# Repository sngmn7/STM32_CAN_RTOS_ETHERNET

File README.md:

# STM32 CAN · Ethernet · FreeRTOS 기반 Zonal E/E Architecture

> STM32 다중 노드와 Jetson을 연계하여 차량의 Zonal E/E Architecture를 축소 구현한 프로젝트입니다.  
> CAN 기반 노드 통신, Ethernet/UDP 기반 상위 시스템 연동, FreeRTOS 실시간 제어, Linux Character Device Driver, DTC 진단, GUI 모니터링, 4-Layer PCB 설계·제작까지 전체 시스템을 직접 구현하고 검증했습니다.

---

## 1. Project Overview

기존의 기능 중심 MCU 프로젝트에서 확장하여, 여러 제어기가 통신을 통해 협력하는 차량 분산 제어 구조를 구현하는 것을 목표로 진행했습니다.

각 Zone 내부에서는 **CAN**을 이용해 센서·제어·상태 정보를 교환하고, Zone Controller에서 수집한 정보는 **Ethernet/UDP**를 통해 상위 시스템인 Jetson으로 전달하도록 구성했습니다.

또한 시스템 규모가 커지면서 발생하는 통신 오류, 실시간성 문제, 고장 진단 문제를 직접 분석하고 검증했습니다.

### 주요 구현 내용

- STM32 기반 다중 노드 Zonal Architecture 구성
- CAN 기반 Zone 내부 통신
- Ethernet/UDP 기반 STM32 ↔ Jetson 연동
- V-Cycle 관점의 요구사항 및 검증 기준 정의
- CAN ID / Data Structure 기반 ICD 작성
- FreeRTOS 기반 실시간 Task 구조 구현
- Linux Character Device Driver 구현
- DTC 기반 고장 진단 시스템
- GUI 기반 시스템 상태 모니터링
- CAN/Ethernet End-to-End Latency 계측
- KiCad 기반 4-Layer PCB 설계 및 실제 제작
- 반복시험 및 자동화된 검증 환경 구성

---

## 2. System Architecture

```text
                  ┌────────────────────────────┐
                  │       Jetson / Linux       │
                  │                            │
                  │  Character Device Driver   │
                  │  DTC / GUI / Monitoring    │
                  └─────────────┬──────────────┘
                                │
                         Ethernet / UDP
                                │
            ┌───────────────────┴───────────────────┐
            │                                       │
┌───────────▼───────────┐               ┌───────────▼───────────┐
│ Front Zone Controller │               │ Rear Zone Controller  │
│     STM32H723         │               │      STM32H723        │
└───────────┬───────────┘               └───────┬─────────┬─────┘
            │ CAN                               │ CAN     │ CAN
            │                                   │         │
     ┌──────▼──────┐                     ┌──────▼───┐ ┌──▼──────────┐
     │ Front Node  │                     │Rear Node │ │Rear Body    │
     │ STM32F407   │                     │STM32F446 │ │STM32F407   │
     └─────────────┘                     └──────────┘ └─────────────┘
```

### 통신 구조
- Zone 내부의 MCU 간 상태 및 제어 데이터 교환
- 센서 데이터 전달
- DTC 및 성능 계측 데이터 전달
- GUI/HMI와 임베디드 제어 시스템 연동

---

## 3. Repository Structure

```text
STM32_CAN_RTOS_ETHERNET/
│
├── Node_F407_Front/
│   └── Front Zone I/O Node
│
├── Node_F407_Rear/
│   └── Rear Body Node
│
├── Node_F447_Rear/
│   └── Rear Zone Sensor Node
│       ※ 실제 MCU는 STM32F446 계열
│
├── ZoneController_Front_H723/
│   └── Front Zone Controller
│
├── ZoneController_Rear_H723_real/
│   └── Rear Zone Controller
│
├── jetson_device_driver/
│   └── Linux Character Device Driver
│
├── jetson_device_driver_lcd/
│   └── I2C LCD Character Device Driver
│
├── rear_node_board/
│   └── KiCad 4-Layer PCB 설계 및 제조 데이터
│
├── DEBUG_JOURNAL_최종/
│   └── Debug / Measurement / Verification Records
│
└── README.md
```

---

# 4. CAN Communication

- 노드별 송수신 역할 정의
- Bit Timing 설정
- CAN Filter 구성
- CAN 상태 및 오류 계측
- 정상/이상 네트워크 비교 검증

---

## 4.1 CAN Frame Loss 47% → 0%

시스템 검증 과정에서 특정 500 kbps CAN Bus에서 수신 프레임의 약 47%가 유실되는 문제가 발생했습니다.

단순히 코드를 수정하기보다 정상 동작하는 CAN 네트워크와 문제가 발생하는 네트워크의 설정을 비교했습니다.

그 결과 두 노드의 **Bit Timing과 Sample Point가 서로 다르게 설정되어 있음**을 확인했습니다.

설정을 정합한 뒤 다시 시험한 결과 프레임 유실률을 0%까지 개선했습니다.

```text
Before : Frame Loss 47 %
After  : Frame Loss 0 %
```

이 경험을 통해 통신 오류 발생 시 정상 시스템을 대조군으로 두고 설정과 데이터를 단계적으로 비교하는 방식의 중요성을 확인했습니다.

---

# 5. Ethernet / UDP Communication

각 Zone에서 수집한 데이터를 상위 시스템인 Jetson으로 전달하기 위해 Ethernet을 사용했습니다.

### 수행 내용

- STM32H723 Ethernet 설정
- lwIP 기반 UDP 통신
- Zone Controller → Jetson Telemetry 전달
- Jetson → Zone Controller Command 전달
- Zone 간 정보 전달
- DTC 및 성능 계측 데이터 전송

CAN은 **Zone 내부의 실시간 데이터 교환**, Ethernet은 **상위 시스템과의 데이터 연동**에 사용하도록 역할을 분리했습니다.

---

# 6. End-to-End Latency Optimization

센서 입력부터 Jetson 상위 시스템까지 데이터가 전달되는 전체 경로를 측정한 결과 최대 **150.6 ms**의 지연이 발생했습니다.

처음에는 개별 코드의 연산시간을 의심했지만, 구간별 시간을 직접 측정한 결과 기존의 **주기 처리 방식**에서 데이터가 준비된 뒤에도 다음 처리 시점까지 대기하는 시간이 반복되고 있음을 확인했습니다.

이에 상행/하행 데이터 처리를 필요한 이벤트가 발생했을 때 수행하도록 **Event Trigger 방식**으로 변경했습니다.

| 항목 | 개선 전 | 개선 후 |
|---|---:|---:|
| 최대 End-to-End Latency | 150.6 ms | 27.5 ms |
| 평균 End-to-End Latency | 65.5 ms | 6.0 ms |
| 최대 지연 개선 | - | **81.7% 감소** |

단순히 코드를 빠르게 만드는 것이 아니라 전체 데이터 흐름을 측정하고 병목 구조를 변경하는 방식으로 문제를 해결했습니다.

---

# 7. FreeRTOS

STM32 Zone Controller의 기능을 Task 단위로 분리하고 실시간 시스템의 동작을 검증하기 위해 FreeRTOS를 적용했습니다.

### 주요 내용

- Task Priority 설계
- Semaphore
- Mutex
- Task Notification
- 공유 자원 동기화
- Stack Usage 계측
- Priority Inversion 검증
- Priority Inheritance 적용

---

## 7.1 Priority Inversion

공유 자원에 접근하는 여러 Task가 동시에 동작할 때 높은 우선순위 Task가 즉시 수행되지 못하는 Priority Inversion 상황을 구성하고 직접 계측했습니다.

Binary Semaphore와 Mutex 사용 시의 차이를 비교했습니다.

| 방식 | 최대 지연 |
|---|---:|
| Semaphore / Priority Inheritance 없음 | 7,096 μs |
| Mutex / Priority Inheritance 적용 | 2,068 μs |

Priority Inheritance를 적용해 지연시간을 약 **3.4배 감소**시켰습니다.

이를 통해 RTOS에서 Task Priority만 설정하는 것뿐 아니라 공유 자원의 동기화 방식까지 실시간 성능에 영향을 준다는 점을 확인했습니다.

---

# 8. FreeRTOS Debugging

FreeRTOS 전환 과정에서는 단순 HardFault가 아닌 Kernel 정지 현상도 경험했습니다.

초기에는 assert가 발생한 위치를 각각 수정했지만 문제 발생 위치가 계속 바뀌었습니다.

이를 메모리 오염 가능성으로 판단하고 Stack Overflow Hook과 High Water Mark를 추가해 Task별 Stack 사용량을 측정했습니다.

그 결과 Ethernet Interface Thread의 Stack이 실제 필요량보다 작게 설정되어 있었음을 확인했습니다.

### 원인

CMSIS-RTOS v2의 `stack_size` 단위를 잘못 해석해 Stack 공간이 부족하게 설정되어 있었습니다.

Stack 크기를 조정한 뒤 반복 시험을 통해 Kernel 정지와 Stack Overflow가 발생하지 않음을 확인했습니다.

이 과정은 `DEBUG_JOURNAL_최종/`에 기록되어 있습니다.

---

# 9. DTC Diagnostic System

시스템 이상이 발생할 때마다 여러 MCU와 통신 로그를 각각 확인해야 해 원인을 파악하는 데 시간이 걸렸습니다.

이를 개선하기 위해 각 노드의 고장 상태를 **DTC(Diagnostic Trouble Code)** 형태로 코드화했습니다.

### 구현 내용

- Node Fault 상태 정의
- DTC Code 정의
- Pending / Confirmed 상태 관리
- CAN Fault Monitoring
- 통신 Timeout Detection
- Ethernet을 통한 DTC 전달
- Jetson GUI에서 Fault 상태 표시
- 반복시험을 통한 진단 결과 검증

---

## 9.1 CAN Link Failure Detection

초기에는 CAN Bus-Off 상태만으로 통신 이상을 판정했습니다.

하지만 실제 CAN Link가 끊겨도 Bus-Off에 진입하지 않아 고장을 감지하지 못하는 경우가 발생했습니다.

이에 Bus-Off뿐 아니라 **수신 데이터 Timeout**을 함께 진단 조건으로 사용하도록 수정했습니다.

```text
CAN Link Failure Detection

Before : 일부 링크 단절 검출 불가
After  : 약 500 ms 이내 검출
```

단순 오류 Flag에만 의존하지 않고 실제 통신 상태까지 함께 확인하도록 진단 기준을 변경했습니다.

---

# 10. GUI / HMI Monitoring

Jetson에서 각 Zone의 상태를 통합해 확인할 수 있도록 GUI 기반 HMI를 구현했습니다.

### 확인 정보

- Zone 상태
- CAN 상태
- 센서 데이터
- DTC
- 통신 상태
- Fault 위치
- System Telemetry

이를 통해 고장 발생 시 여러 Node의 로그를 각각 확인하기 전에 GUI에서 먼저 이상 위치와 상태를 파악할 수 있도록 구성했습니다.

반복적인 Closed-Loop 시험을 통해 HMI와 실제 시스템 동작을 검증했습니다.

---

# 11. Linux Character Device Driver

Jetson Linux 환경에서 Kernel Space와 User Space 간 HW/SW Interface를 직접 구현하기 위해 Character Device Driver를 작성했습니다.

---

## 11.1 I2C LCD Driver

PCF8574 기반 I2C LCD를 제어하는 Linux Character Device Driver를 구현했습니다.

### 구현 내용

- `i2c_driver`
- `probe()` / `remove()`
- Character Device 등록
- `/dev` Interface 제공
- `open`
- `write`
- `ioctl`
- Mutex 기반 동기화
- LCD Command 처리

User Space Application이 `/dev`를 통해 LCD 기능을 사용할 수 있도록 구성했습니다.

---

## 11.2 UDP Status Driver

Zone Controller에서 전달되는 UDP Telemetry를 Linux Kernel에서 수신하고 `/dev` Interface를 통해 User Space에 제공하는 Driver를 구현했습니다.

### 구현 내용

- Kernel UDP Socket
- Kernel Thread
- Blocking Read
- Wait Queue
- Spinlock
- `poll()`
- Packet Validation
- Sequence Monitoring

초기에는 SocketCAN Network Device 형태로 구현하려 했지만, CAN Subsystem이 요구하는 초기화 조건을 충족하지 못해 Kernel이 정지하는 문제가 발생했습니다.

Kernel UDP Socket과 Thread는 정상 동작하고 있음을 확인한 뒤 Network Device 등록 계층을 분리해 문제를 좁혔고, Character Device 방식으로 변경해 해결했습니다.

---

# 12. PCB Design & Manufacturing

초기 시스템은 Breadboard와 Jumper Wire를 이용해 구성했습니다.

프로젝트가 커지면서 다음 문제가 반복적으로 발생했습니다.

- 접촉 불량
- 배선 복잡도 증가
- CAN 배선 오류 가능성
- 재현성이 낮은 HW 구성

이를 개선하기 위해 KiCad를 이용해 **4-Layer Custom PCB를 직접 설계하고 실제 제작업체에 제조를 의뢰했습니다.**

### 수행 과정

1. 기존 배선 및 Pin Map 정리
2. 회로도 작성
3. CAN Transceiver 회로 구성
4. CAN Termination 설계
5. Sensor / Actuator Interface 설계
6. Power / Signal Net 정의
7. Footprint 배치
8. 4-Layer Stack 구성
9. Routing
10. ERC / DRC 검증
11. Gerber 및 Drill File 생성
12. 외부 PCB 제조 의뢰
13. 실제 보드 제작 및 시스템 적용

---

## 12.1 CAN Hardware Design

CAN 통신부에는 SN65HVD230 기반 CAN Transceiver와 Split Termination 구조를 적용했습니다.

Rear CAN Network에서는 3개의 Node가 연결되므로 버스의 양 끝 Node에만 Termination을 적용할 수 있도록 Jumper 구조를 구성했습니다.

센서, LED, Switch 및 기타 I/O 회로도 PCB에 통합했습니다.

PCB 관련 설계 파일 및 제조 데이터는 아래 폴더에 있습니다.

```text
rear_node_board/
```

---

# 13. V-Cycle & ICD

프로젝트 규모가 커지면서 여러 Node의 기능과 통신 기준을 기억에 의존해 관리하기 어려워졌습니다.

이에 V-Cycle 관점에서 요구사항과 검증 기준을 정리했습니다.

### 수행 내용

- System Requirement 정의
- Functional Requirement 분해
- 검증 기준 작성
- CAN ID 정의
- CAN Data Structure 정의
- UDP Packet 정의
- Interface Control Document 작성
- Test Case 구성
- 요구사항 ↔ 검증 항목 연결

기능 구현 이후 시험 방법을 생각하는 것이 아니라 요구사항 정의 단계에서 검증 방법까지 함께 고려하도록 개발 방식을 정리했습니다.

---

# 14. Debugging & Verification

프로젝트 과정에서 발생한 문제와 분석 과정을 별도의 Debug Journal로 관리했습니다.

```text
DEBUG_JOURNAL_최종/
```

### 주요 Debugging 사례

- CAN Frame Loss
- CAN Bit Timing / Sample Point 문제
- Ethernet Power-On Failure
- FreeRTOS Stack Overflow
- Priority Inversion
- DTC False Detection
- CAN Link Failure Detection
- UDP Telemetry 검증
- Network IP / Subnet 문제
- Sensor Data 이상
- Closed-Loop System Verification

단순히 해결 결과만 기록하지 않고 아래와 같은 형태로 관리했습니다.

```text
Problem
  ↓
Hypothesis
  ↓
Measurement
  ↓
Root Cause
  ↓
Modification
  ↓
Regression Test
```

---

# 15. Measurement & Verification

시스템 동작을 감으로 판단하지 않고 가능한 항목은 실제 데이터를 측정해 검증했습니다.

### 대표 검증 항목

| 항목 | 결과 |
|---|---:|
| CAN Frame Loss | 47% → 0% |
| End-to-End Maximum Latency | 150.6 ms → 27.5 ms |
| End-to-End Average Latency | 65.5 ms → 6.0 ms |
| Priority Inversion Delay | 7,096 μs → 2,068 μs |
| CAN Link Failure Detection | 검출 불가 → 약 500 ms |
| DTC 반복 검출 편차 | 약 1.5 ms 수준 |
| HMI Closed-Loop Test | 8 / 8 Pass |

---

# 16. Tech Stack

### Embedded

- STM32H723
- STM32F407
- STM32F446
- C
- STM32CubeIDE
- STM32 HAL
- FreeRTOS
- CMSIS-RTOS2

### Communication

- CAN
- FDCAN
- Ethernet
- UDP
- I2C
- RS485

### Linux

- Jetson
- Linux Kernel Module
- Character Device Driver
- Kernel UDP Socket
- Kernel Thread
- `/dev` Interface

### Hardware

- KiCad
- 4-Layer PCB
- CAN Transceiver
- Gerber
- BOM
- PCB Manufacturing

### System Engineering

- V-Cycle
- ICD
- DTC
- Test Case
- System Integration
- Verification
- Debugging

---

# 17. Key Takeaways

이 프로젝트에서는 단순히 MCU의 기능을 구현하는 것을 넘어 여러 장치가 연결된 시스템 전체를 설계하고 검증했습니다.

특히 다음을 직접 경험했습니다.

- CAN / Ethernet 기반 분산 통신 구조 설계
- 통신 오류의 Root Cause 분석
- FreeRTOS 기반 실시간 시스템 설계
- Task Synchronization 및 Priority Inversion 검증
- Linux Kernel Device Driver 구현
- DTC 기반 고장 진단
- GUI 기반 상태 모니터링
- V-Cycle과 ICD를 활용한 Interface 관리
- 4-Layer PCB 설계 및 실제 제작
- HW / FW / Linux를 포함한 전체 시스템 통합
- 측정 데이터를 기반으로 한 성능 개선 및 Regression Test

기능이 한 번 동작하는 것보다 **문제가 발생했을 때 원인을 추적할 수 있고, 수정한 결과를 다시 검증할 수 있는 시스템을 만드는 것**을 목표로 프로젝트를 진행했습니다.

---

## Author

**Lee Seungmin**

- Kyungpook National University
- Department of Electronics Engineering
- CAN ID 대역 정의
- 메시지별 Data Structure 정의
각 Zone 내부의 MCU 간 통신은 CAN을 기반으로 구성했습니다.

### 수행 내용
- 액추에이터 명령 전달
- 고장 및 상태 정보 전달

**Ethernet / UDP**
- 각 Zone Controller에서 수집한 데이터를 Jetson으로 전달
- 상위 시스템 명령 전달

CAN과 Ethernet은 서로 다른 역할로 사용했습니다.
**CAN**

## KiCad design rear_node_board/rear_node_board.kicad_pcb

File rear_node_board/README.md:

# REAR NODE BOARD — STM32F446RET6 ×2

Rear 존의 말단 두 노드를 **한 장의 PCB**로 합친 보드.
H723 존 컨트롤러는 **Nucleo-144 모듈 그대로** 두고 J2 로 연결한다.

```
[H723 Nucleo-144]  ── J2 (CAN 로직신호 4 + GND) ──┐
                                                   │
   ┌───────────────── REAR NODE BOARD ─────────────┴──────────────┐
   │  U3 ─ CAN500 ─ U4 ─ U1 (F446RET6, rear body)                 │
   │  U5 ─ CAN250 ─ U6 ─ U2 (F446RET6, 센서/램프 노드)             │
   │                        └ LED×4, 스위치, HC-SR04, BNO085      │
   └──────────────────────────────────────────────────────────────┘
              │
        J5 ── REAR-CAN-H 500k → 모터 노드(외부)
```

**검증 상태**: ERC **0 errors / 0 warnings**, 배치검사 통과,
두 MCU **각각 64/64 핀 전부 연결**(미연결은 트랜시버 Vref ×4, 의도된 NC).

### 배선 방식

**436개 배선 + 51개 정션**으로 실제 선이 그려져 있다. 라벨만 띄워놓은 게 아니다.

| 실선으로 그린 것 | 방식 |
|---|---|
| CAN 500k / 250k 버스 | 세로 트렁크 + 각 노드로 가지 + 정션 |
| 종단 5세트 | JP→60R→중점→60R→CANL 직렬 체인, 중점에서 4.7nF→GND |
| LED 4개 | 저항→애노드 실선, 캐소드→GND |
| 크리스탈 2개 | 크리스탈↔로드캡 실선, 캡→GND |
| 스위치 + 풀업 | 같은 노드로 실선 결선 |
| 디커플링 15개 | 위쪽 +3V3 레일 / 아래쪽 GND 레일 실선 + 정션 |

**MCU 두 개만 네트 라벨을 쓴다.** 핀 128개를 시트 전체로 배선하면 오히려
읽을 수 없어지기 때문이고, 이건 실무 회로도의 표준 방식이다.
전기적 연결은 동일하며 네트리스트로 검증했다.

### ★ 네트 라벨 = 실제 배선이다

**PCB 는 회로도의 선 그림을 보지 않는다. 네트리스트만 읽는다.**
그래서 라벨로 연결하든 선으로 연결하든 PCB 결과는 완전히 같다.

이것을 말이 아니라 실물로 확인했다 — 이 회로도에서 PCB 를 실제로 생성했다.

```
netlist : 83 components, 136 nets
placed  : 83 footprints        <- 누락 0
nets    : 136 on board, 404 pads assigned
DRC     : 0 violations, 266 unconnected items
```

`266 unconnected items` 가 바로 **rats nest** 다. pcbnew 가 "이 266 개를
연결해야 한다"고 인식했다는 뜻이고, 곧 MCU 핀을 포함한 모든 연결이
정상적으로 넘어갔다는 증거다.

예를 들어 U2(F446) 의 핀들은 PCB 에서 이렇게 이어진다.

```
pin 11  TOGGLE_SW  -> R18.2, SW1.1
pin 14  LED_LEFT   -> R14.1
pin 30  ND_VCAP1   -> C27.1
pin 44  ND_CAN_RX  -> U6.4
pin 61  I2C1_SCL   -> J8.3, R19.2
pin  2  ND_PC13    -> J14.1
```

**64 핀 전부가 이런 식으로 연결돼 있다.**

---

## 1. 왜 F446 두 개인가

원래 rear body 노드는 F407VG(LQFP100)였지만 F446RET6(LQFP64)로 통일했다.

| | 통일 전 | 통일 후 |
|---|---|---|
| MCU 종류 | F407VG + F446RE | **F446RE ×2** |
| 풋프린트 | LQFP100 + LQFP64 | **LQFP64 ×2** |
| 지원회로 | VCAP 2개 + 1개, 서로 다름 | **완전 동일** |
| BOM 라인 | 2 | **1** |

> ⚠️ **펌웨어 이식 필요**: F407 rear body 펌웨어는 CAN1 이 **PD0/PD1** 이었다.
> F446 LQFP64 에는 그 핀이 없어 **PA11/PA12** 로 옮겨야 한다.
> 현재 rear body 는 500k ping/echo(0x101→0x181)만 하므로 이식 부담은 작다.

---

## 2. 보드 구성

| 참조 | 부품 | 역할 |
|---|---|---|
| U1 | STM32F446RET6 | rear body 노드, 500k 버스 |
| U2 | STM32F446RET6 | 센서/램프 노드, 250k 버스 |
| U3 | SN65HVD230 | H723 FDCAN1 ↔ 500k |
| U4 | SN65HVD230 | U1 ↔ 500k |
| U5 | SN65HVD230 | H723 FDCAN2 ↔ 250k |
| U6 | SN65HVD230 | U2 ↔ 250k |
| U7 | AMS1117-3.3 | 5V → 3.3V |
| Y1, Y2 | 8 MHz | HSE |
| JP1~JP5 | 종단 점퍼 | 아래 §3 |

### 커넥터

| 참조 | 용도 | 핀 |
|---|---|---|
| J1 | VIN 5 V | 스크류터미널 2 |
| J2 | **H723 Nucleo** (FDCAN1 TX/RX, FDCAN2 TX/RX, GND×2) | 6 |
| J3 / J4 | SWD (U1 / U2) — 3V3, SWCLK, GND, SWDIO, **NRST**, SWO | 6 |
| J5 | REAR-CAN-H 500k → 모터 노드 | 3 |
| J6 | REAR-CAN-L 250k 예비 | 3 |
| J7 | HC-SR04 (**5 V**) | 4 |
| J8 | BNO085 IMU | 6 |
| J9 | UART 콘솔 (U2) | 3 |
| J10~J13 | U1 브레이크아웃 (43핀 전부) | 12/12/12/11 |
| J14~J16 | U2 브레이크아웃 (30핀 전부) | 12/12/9 |

---

## 3. ★ 종단 점퍼 — 이것만은 틀리면 안 됨

| 버스 | 드롭 | 점퍼 | 기본 |
|---|---|---|---|
| REAR-CAN-H 500k | **3개** (H723, U1, 모터노드) | JP1 (H723) | **삽입** |
| | | JP2 (U1, 버스 중간) | **개방** |
| | | JP3 (모터노드 쪽) | **삽입** |
| REAR-CAN-L 250k | 2개 | JP4, JP5 | **둘 다 삽입** |

3개를 다 끼우면 40 Ω 이 되어 드라이버가 규정 차동전압을 못 만들고 통신이 깨진다.
종단은 스플릿(60 Ω + 60 Ω, 중점 4.7 nF → GND) 방식.

---

## 4. 조립 시 반드시 지킬 것

**① C26 / C27 (VCAP, 각 MCU 30번핀) — 필수**
내부 레귤레이터 안정화용. 없거나 멀면 **칩이 아예 부팅하지 않는다.**
디커플링처럼 "있으면 좋은" 부품이 아니다. 핀 바로 옆에 배치할 것.

**② R2 / R3 (BOOT0 풀다운, 각 60번핀) — 필수**
빠지면 플래시 부팅이 안 되고 무작위로 시스템 부트로더로 들어간다.
커스텀 보드 첫 제작에서 가장 흔한 실패 원인.

**③ SWD 헤더에 NRST 포함**
클럭 설정을 잘못 넣었을 때 connect-under-reset 으로만 살릴 수 있다.
NRST 가 없으면 그대로 벽돌이 된다.

**④ VDD 핀마다 100 nF**
MCU 하나당 VDD 4개(19, 32, 48, 64) → 각각 바로 옆에.

**⑤ J2 의 GND 를 반드시 연결**
H723 Nucleo 는 자기 전원을 쓰지만, 트랜시버가 기준 전위를 공유해야
CAN 이 성립한다. GND 미공통이 CAN 무응답의 가장 흔한 원인이다.

---

## 5. 펌웨어 쪽 확인 사항

**클럭을 HSE 로 바꿔야 한다.**
현재 F446 펌웨어 `SystemClock_Config()` 는 HSI 를 쓴다
(`RCC_OSCILLATORTYPE_HSI`, PLLM=16, PLLN=336, PLLP=4 → 84 MHz).

STM32F4 의 HSI 는 25 °C 에서 ±1 %, 온도 범위 전체로는 더 나빠진다.
CAN 은 통상 **±0.5 % 이하**를 요구하므로 HSI 로는 마진이 없다.
Nucleo 로 책상에서 짧은 배선일 때는 돌아가지만, 실제 배선이 길어지면
마진이 사라진다. **Y1/Y2 를 달았으니 HSE 로 전환할 것.**

---

## 6. PCB 뜰 때

- **2층으로 충분하다.** 최고 속도가 CAN 500 kbps 라 임피던스 제어·길이 매칭 불필요
- 바텀은 통 GND 플레인
- **CANH/CANL 은 반드시 쌍으로 나란히**, 트랜시버→커넥터 스터브 최소화
- LQFP64 는 0.5 mm 피치 — 이것만 주의
- HC-SR04 는 5 V 라 J7 전원만 5 V 레일에서 따온다

---

## 7. 아직 확인 못 한 것

| 항목 | 왜 |
|---|---|
| BNO085 모듈 내부 I2C 풀업 | 있으면 R19/R20 을 빼야 한다 (중복 시 값 반토막) |
| 모터 노드 자체 종단 유무 | 있으면 JP3 를 개방해야 한다 |
| VCAP 정확한 용량 | 2.2 µF 는 ST 표준 권장값. 발주 전 데이터시트 재확인 |

---

## 8. 재생성

```bash
# 회로도 + ERC + 네트리스트 + BOM + PDF
python tools/build.py

# 네트리스트 -> PCB (풋프린트 전부 로드 + 네트 할당 + 개략 배치)
"E:\Program files\bin\python.exe" tools\make_pcb.py rear_node_board
```

회로 수정은 `tools/gen_rear_board.py` 에서. KiCad GUI 에서 직접 고치면
다음 빌드에 덮어써진다.

> `make_pcb.py` 는 **레이아웃 시작점**을 만들어 줄 뿐이다. 부품은 격자에
> 대충 뿌려져 있으니 pcbnew 에서 배치를 정리하고 라우팅하면 된다.
> 이미 만든 배치를 유지하려면 다시 돌리지 말고, 회로도를 고친 뒤
> pcbnew 의 **"회로도에서 PCB 업데이트"** 를 쓰는 편이 낫다.

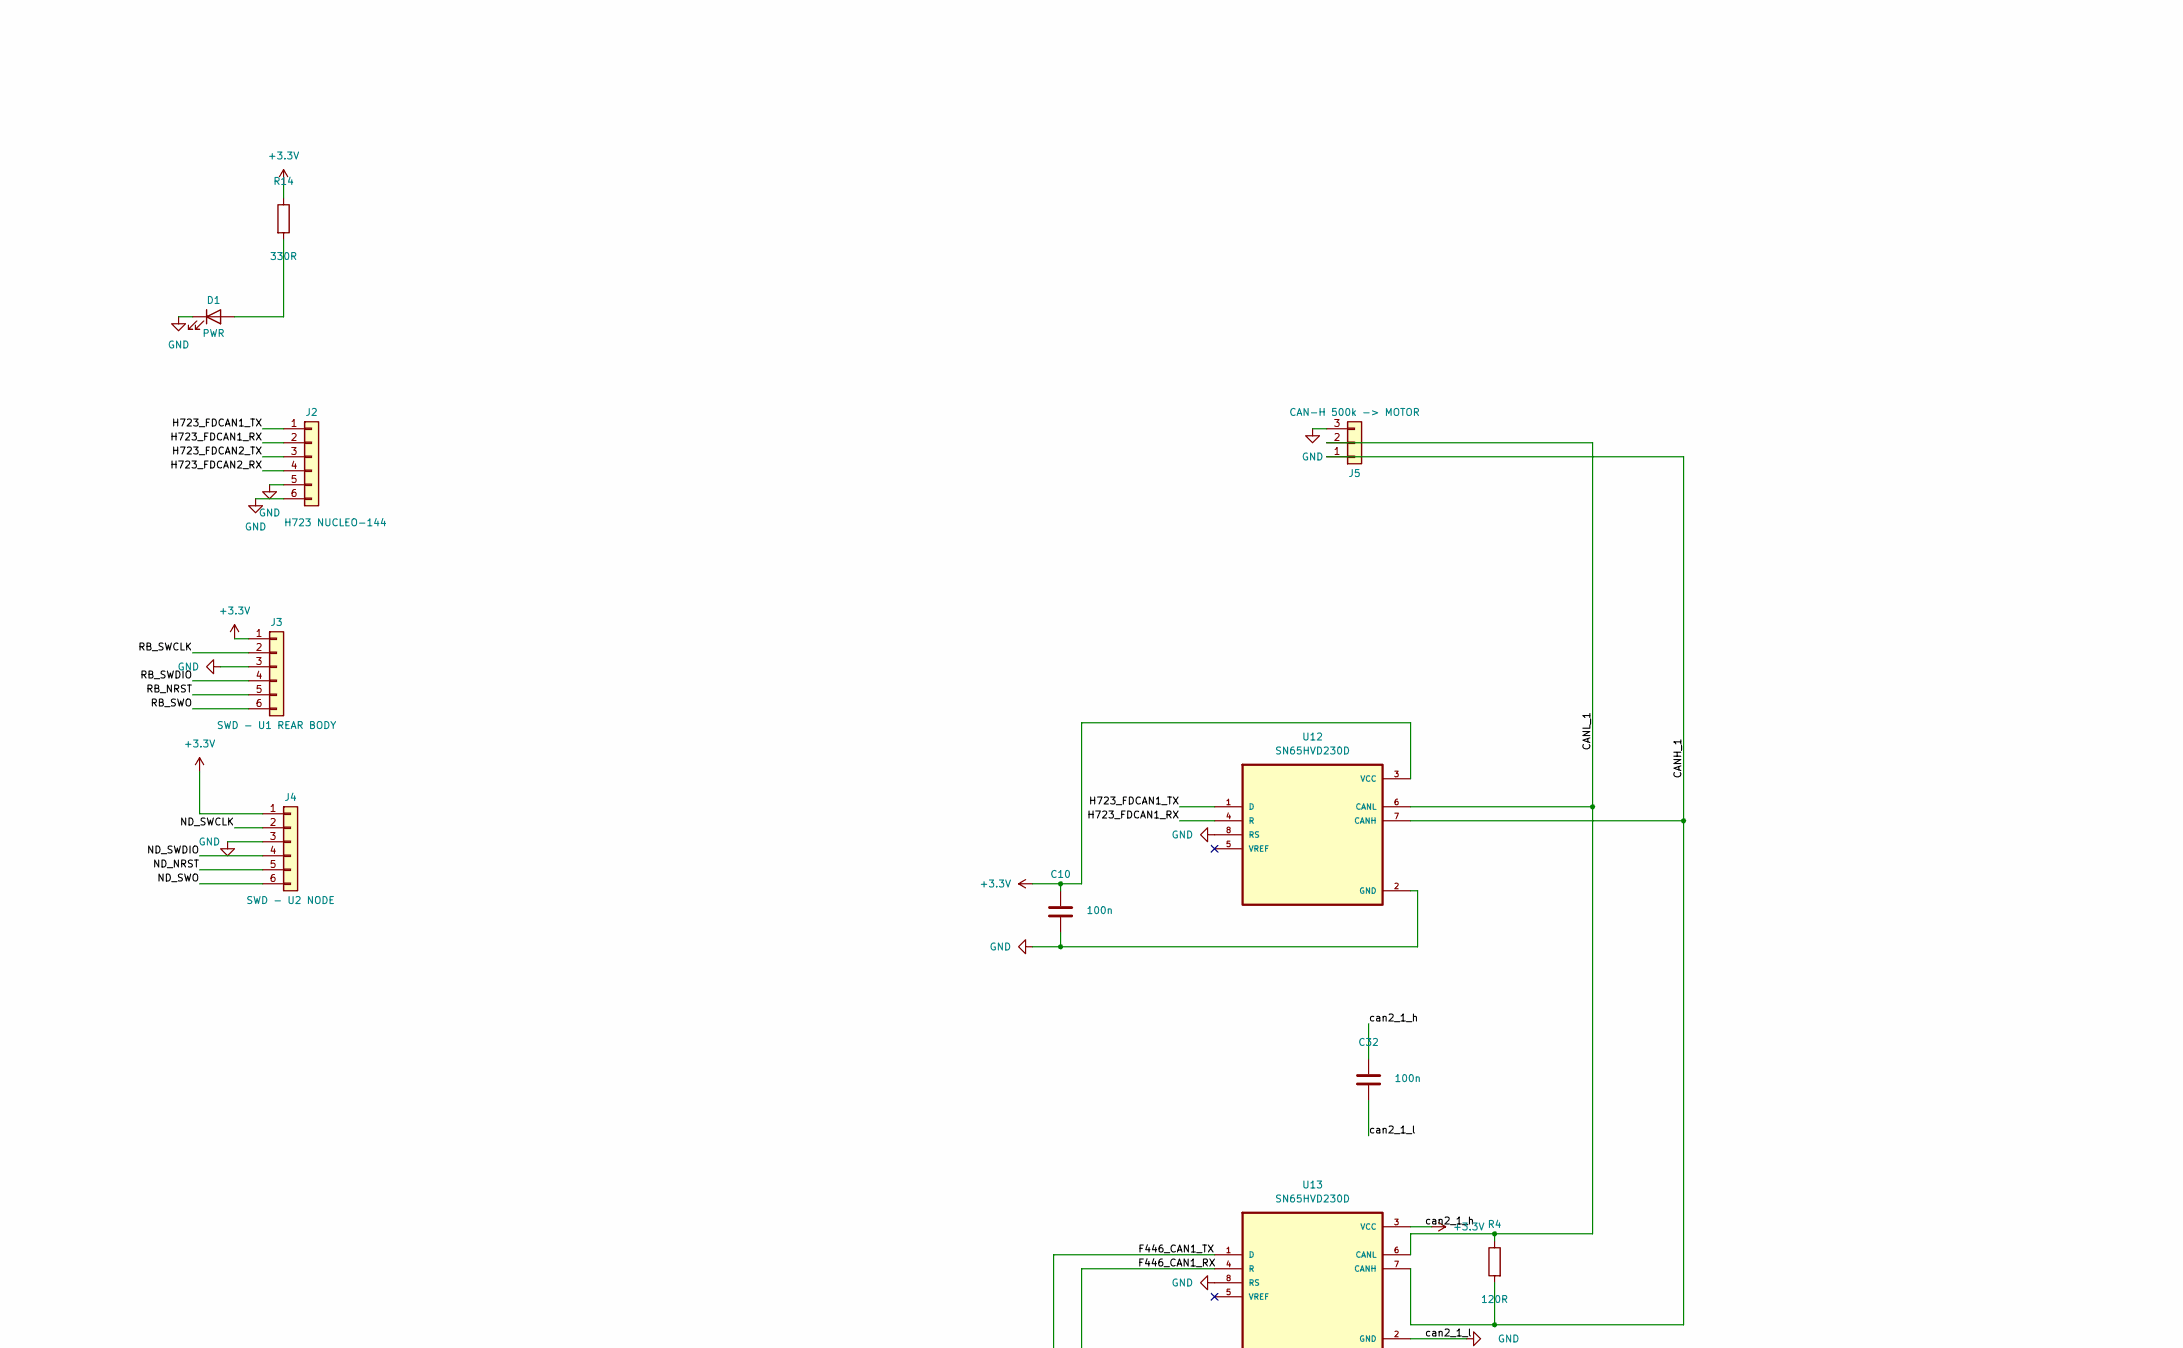
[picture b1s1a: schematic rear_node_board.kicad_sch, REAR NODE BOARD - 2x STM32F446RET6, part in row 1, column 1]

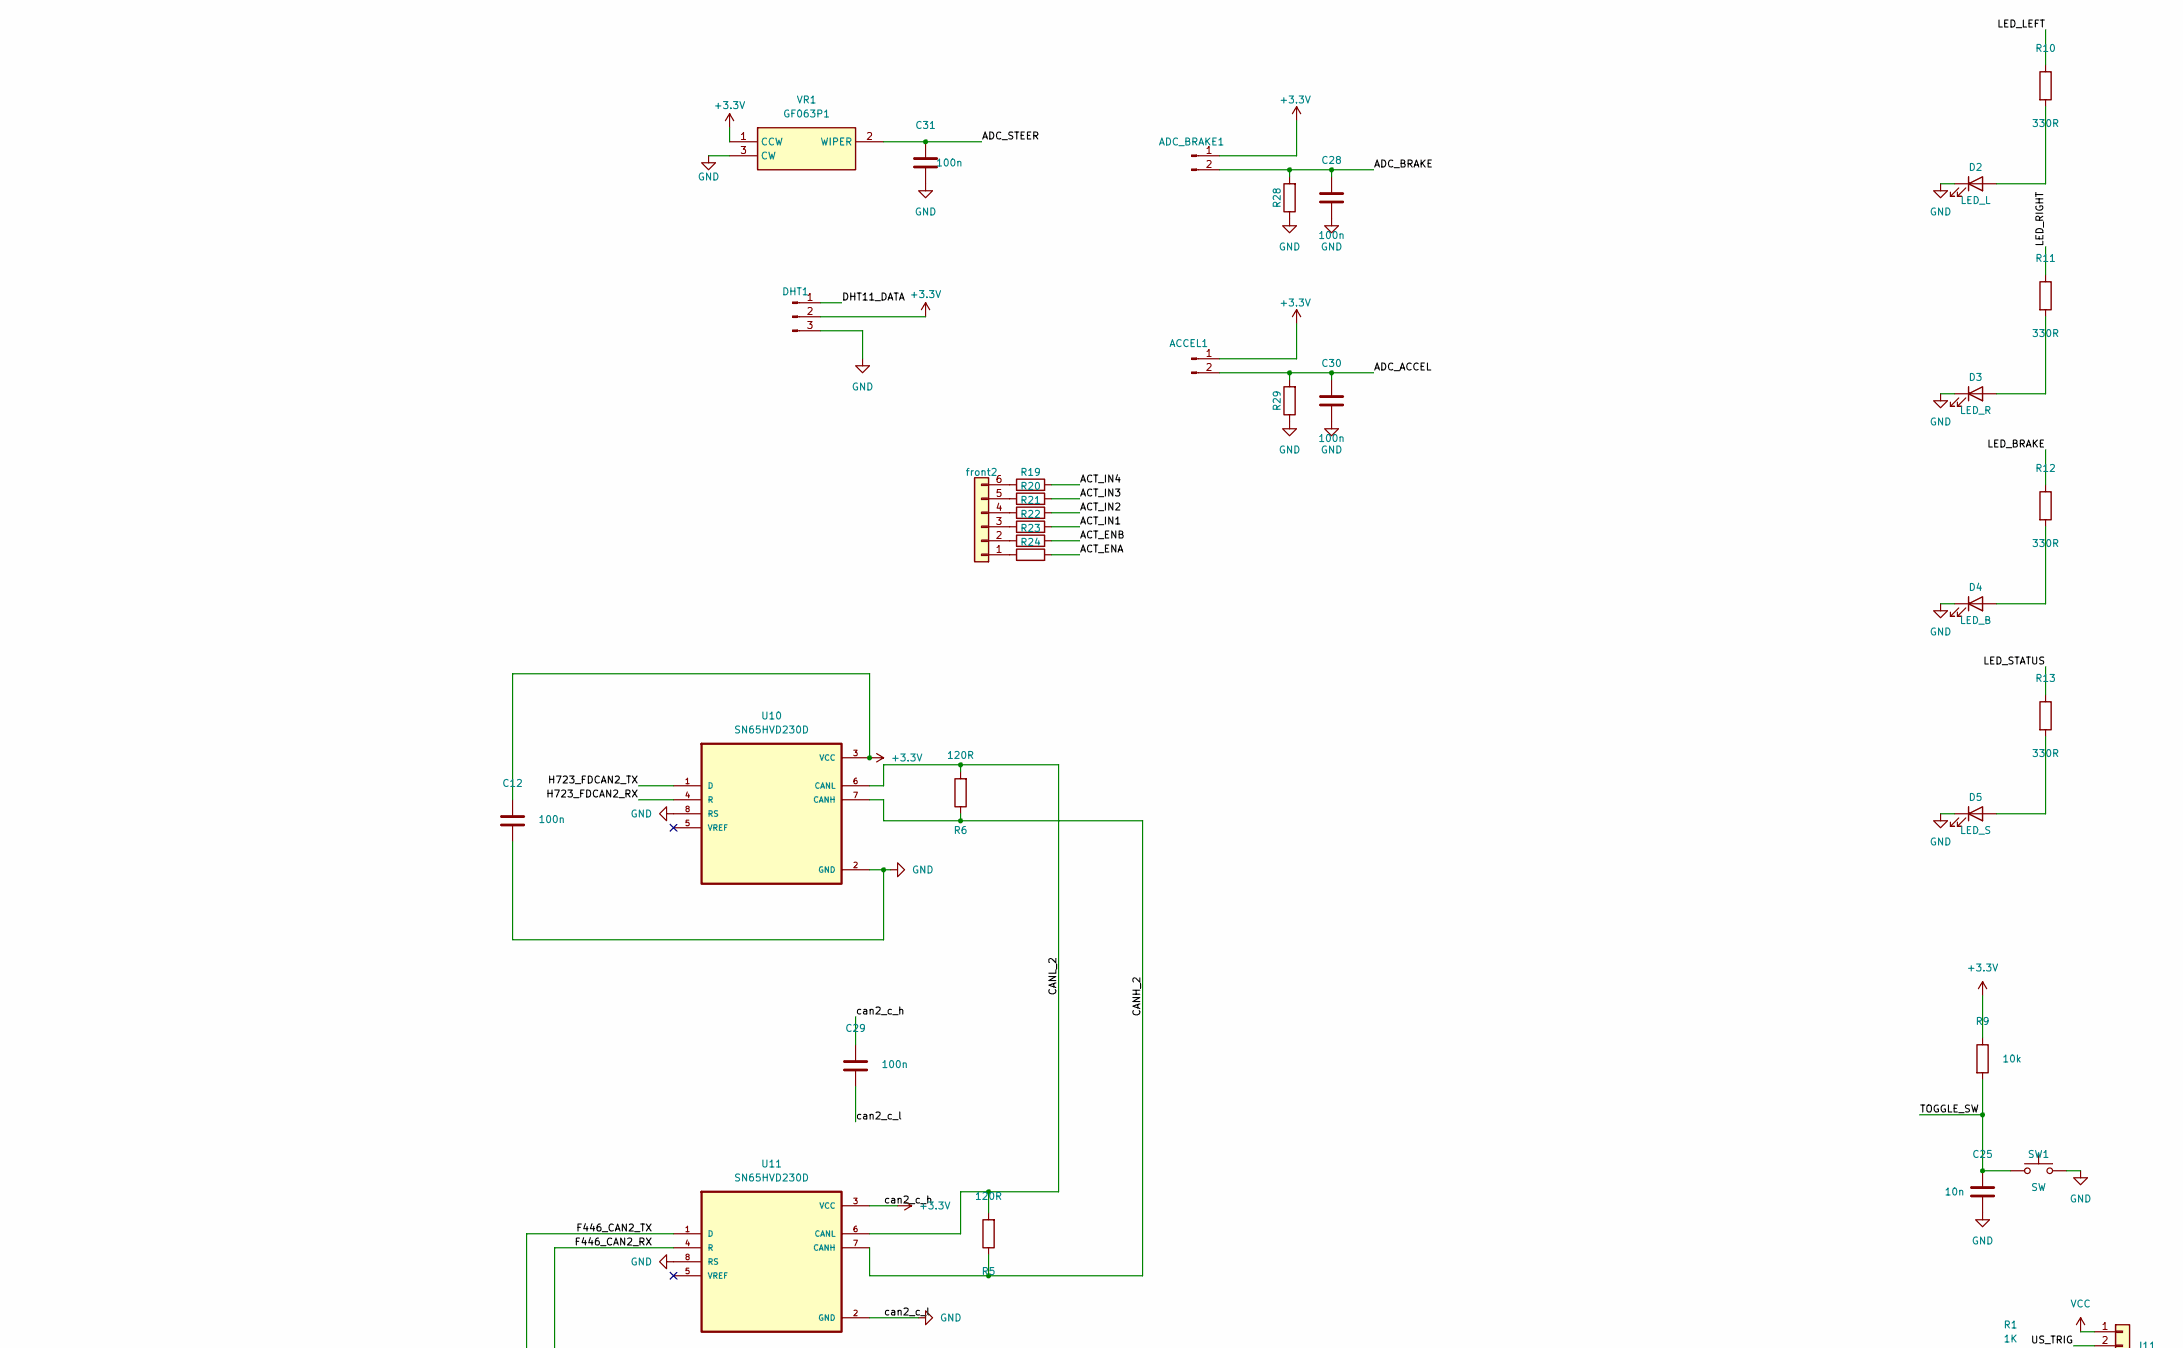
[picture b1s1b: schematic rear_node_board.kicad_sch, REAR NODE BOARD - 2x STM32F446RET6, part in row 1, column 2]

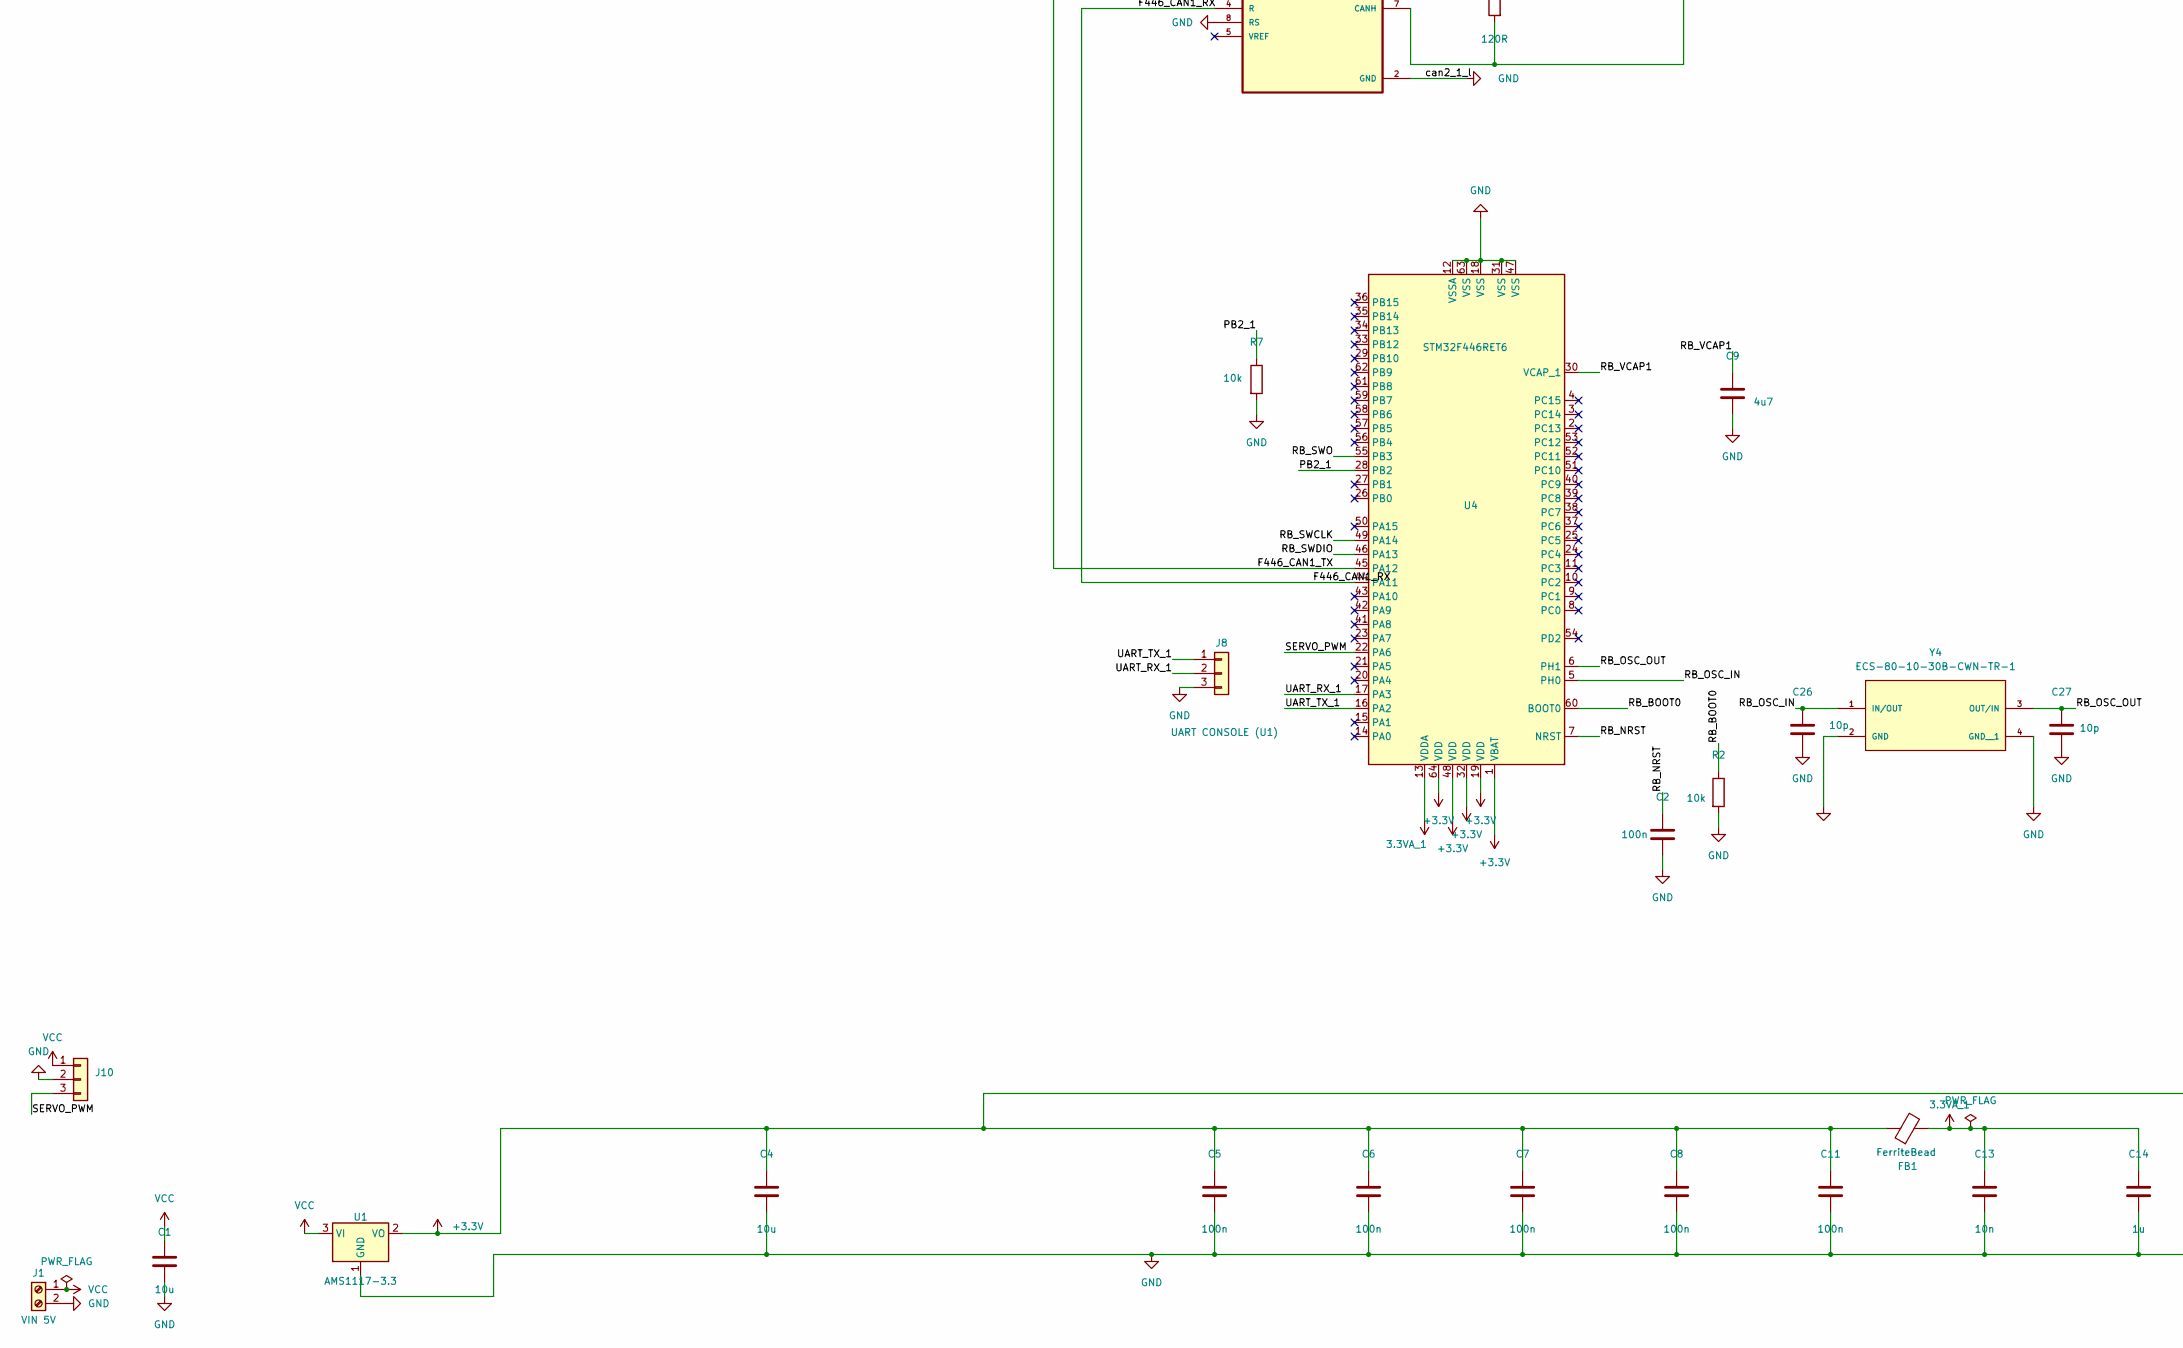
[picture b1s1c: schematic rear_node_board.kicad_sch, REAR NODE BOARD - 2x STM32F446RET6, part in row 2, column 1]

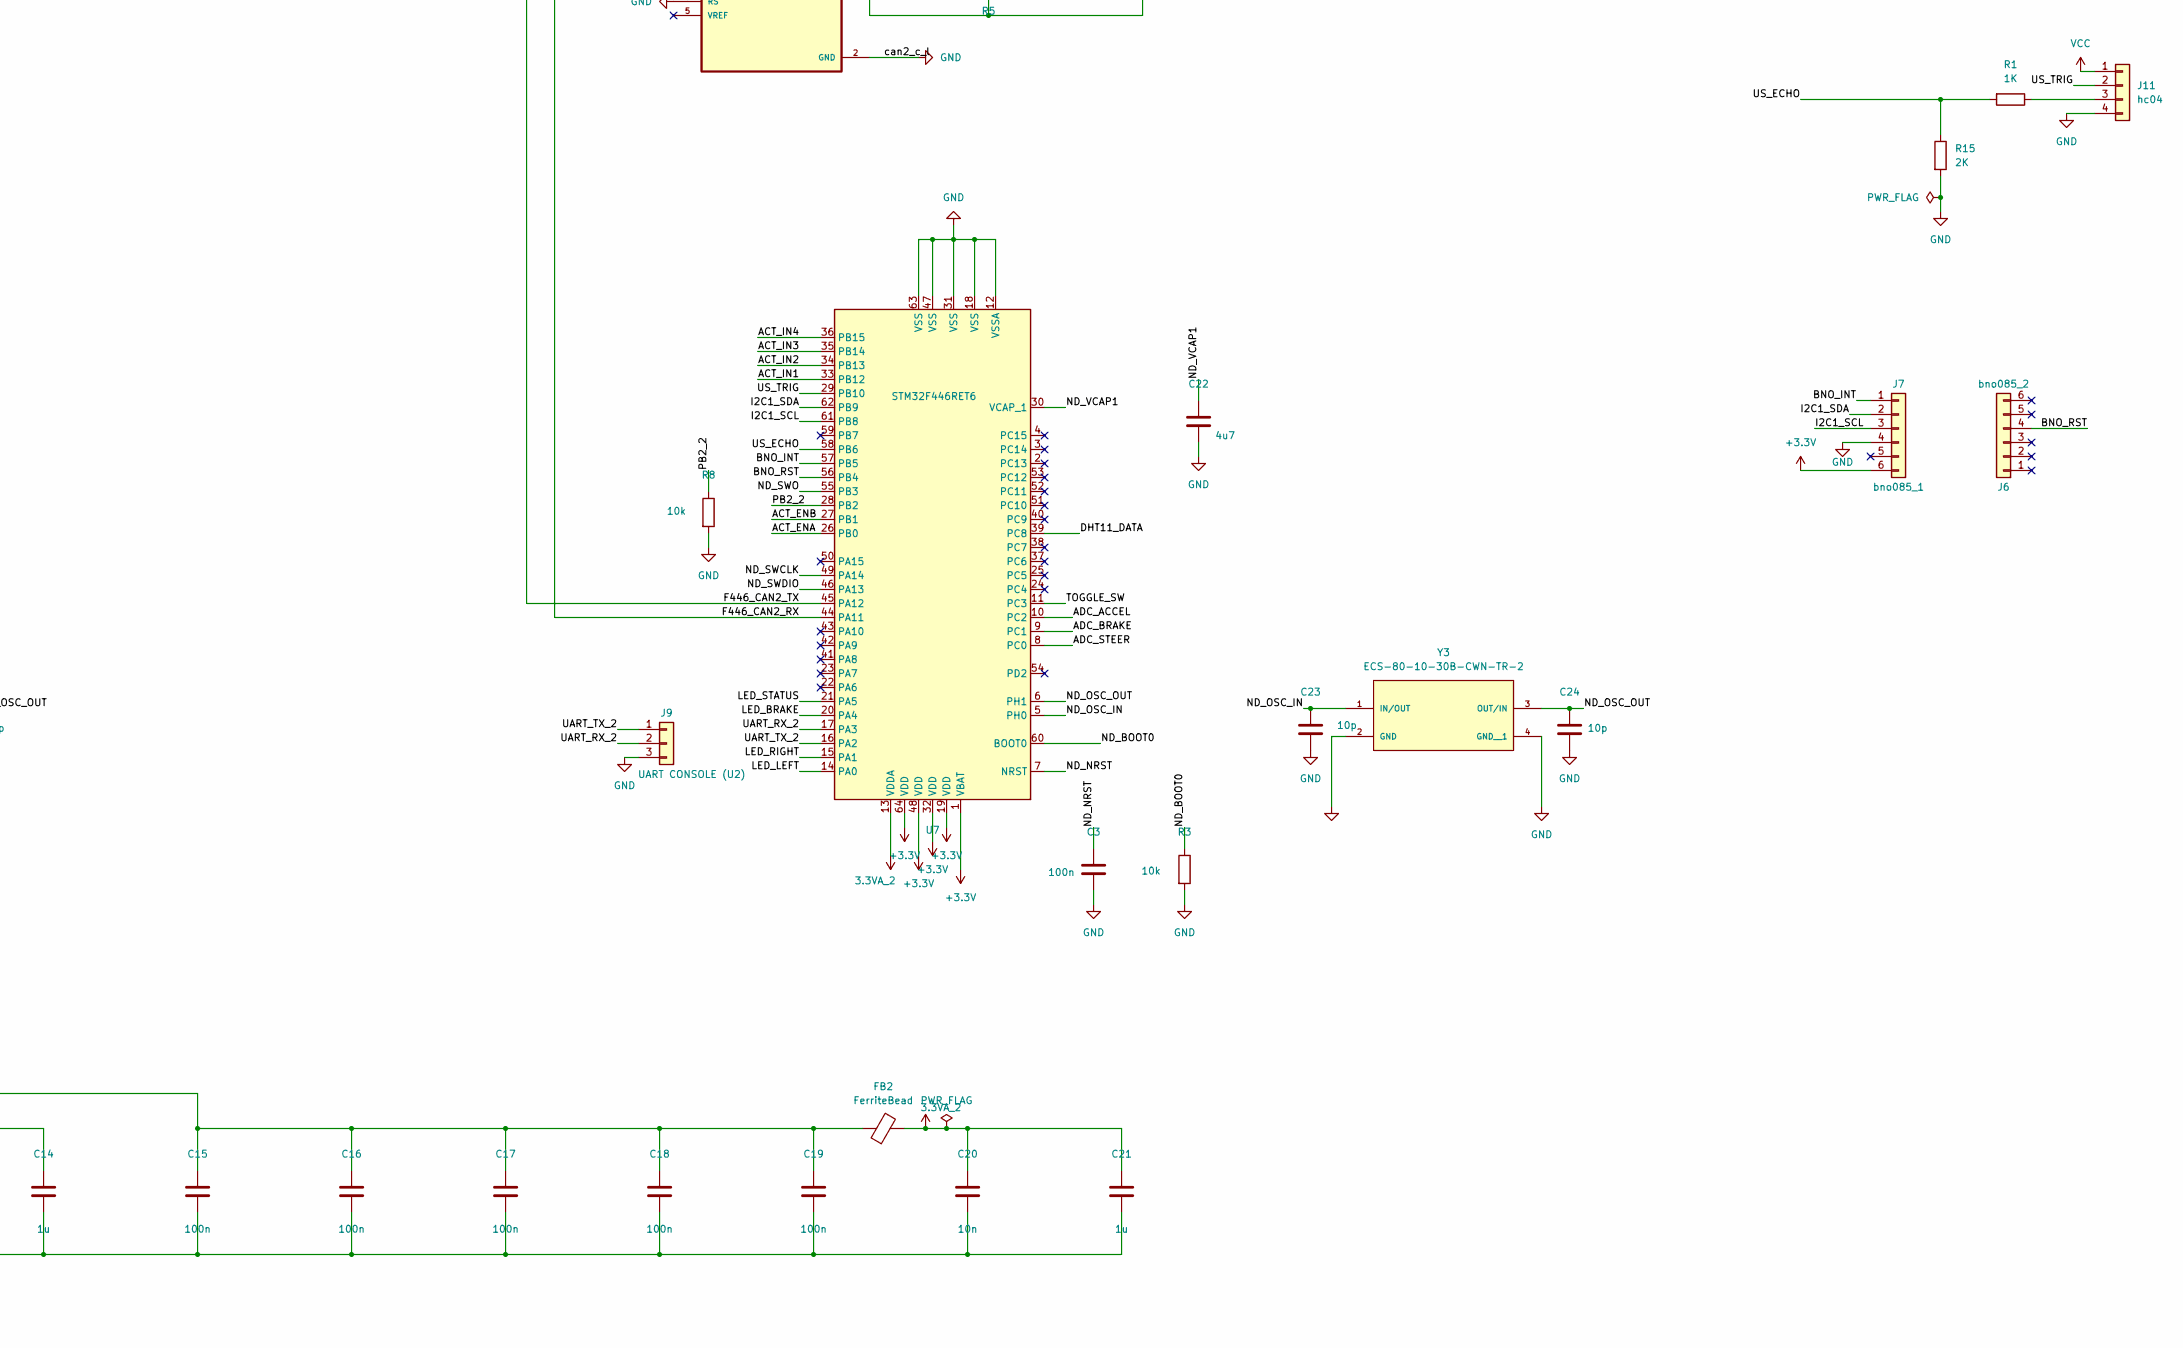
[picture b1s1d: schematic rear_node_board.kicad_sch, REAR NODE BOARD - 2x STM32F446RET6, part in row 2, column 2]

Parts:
ACCEL1: Conn_01x02_Pin; PinHeader_1x02_P2.54mm_Vertical
ADC_BRAKE1: Conn_01x02_Pin; PinHeader_1x02_P2.54mm_Vertical
C1, C4: 10u; CP_Elec_4x5.4
C2, C3, C5, C6, C7, C8, C10, C11, C12, C15, C16, C17, C18, C19, C28, C29, C30, C31, C32: 100n; C_1206_3216Metric
C9, C22: 4u7; CP_Elec_4x5.3
C13, C20, C25: 10n; C_0603_1608Metric
C14, C21: 1u; CP_Elec_4x5.4
C23, C24, C26, C27: 10p; C_1206_3216Metric
D1: PWR; LED_D5.0mm
D2: LED_L; LED_D5.0mm
D3: LED_R; LED_D5.0mm
D4: LED_B; LED_D5.0mm
D5: LED_S; LED_D5.0mm
DHT1: Conn_01x03_Pin; PinHeader_1x03_P2.54mm_Vertical
FB1, FB2: FerriteBead; R_0805_2012Metric
J1: VIN 5V; TerminalBlock_Phoenix_MKDS-1,5-2-5.08_1x02_P5.08mm_Horizont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
J2: H723 NUCLEO-144; PinHeader_1x06_P2.54mm_Vertical
J3: SWD - U1 REAR BODY; PinHeader_1x06_P2.54mm_Vertical
J4: SWD - U2 NODE; PinHeader_1x06_P2.54mm_Vertical
J5: CAN-H 500k -> MOTOR; PinHeader_1x03_P2.54mm_Vertical
J6: bno085_2; PinHeader_1x06_P2.54mm_Vertical
J7: bno085_1; PinHeader_1x06_P2.54mm_Vertical
J8: UART CONSOLE (U1); PinHeader_1x03_P2.54mm_Vertical
J9: UART CONSOLE (U2); PinHeader_1x03_P2.54mm_Vertical
J10: Conn_01x03; PinHeader_1x03_P2.54mm_Vertical
J11: hc04; PinHeader_1x04_P2.54mm_Vertical
R1: 1K; R_0805_2012Metric
R2, R3, R7, R8, R9: 10k; R_0805_2012Metric
R4, R5, R6: 120R; R_0805_2012Metric
R10, R11, R12, R13, R14: 330R; R_0805_2012Metric
R15: 2K; R_0805_2012Metric
R19, R20, R21, R22, R23, R24: 330; R_0805_2012Metric
R28, R29: 1k; R_0805_2012Metric
SW1: SW; SW_PUSH_6mm
U1: AMS1117-3.3; SOT-223-3_TabPin2
U4, U7: STM32F446RET6; LQFP-64_10x10mm_P0.5mm
U10, U11, U12, U13: SN65HVD230D; SOIC127P599X175-8N
VR1: GF063P1; Manufacturer_Part_Number GF063P1
Y3: ECS-80-10-30B-CWN-TR-2; XTAL_ECS-80-10-30B-CWN-TR
Y4: ECS-80-10-30B-CWN-TR-1; XTAL_ECS-80-10-30B-CWN-TR
front2: Conn_01x06; PinHeader_1x06_P2.54mm_Vertical

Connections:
3.3VA_1: C13.1, C14.1, FB1.2, U4.13 (VDDA)
3.3VA_2: C20.1, C21.1, FB2.2, U7.13 (VDDA)
+3.3V: ACCEL1.1, ADC_BRAKE1.1, C4.1, C5.1, C6.1, C7.1, C8.1, C10.1, C11.1, C12.1, C15.1, C16.1, C17.1, C18.1, C19.1, C29.1, C32.1, DHT1.2, FB1.1, FB2.1, J3.1, J4.1, J7.6, R9.1, R14.1, U1.2 (VO), U4.1 (VBAT), U4.19 (VDD), U4.32 (VDD), U4.48 (VDD), U4.64 (VDD), U7.1 (VBAT), U7.19 (VDD), U7.32 (VDD), U7.48 (VDD), U7.64 (VDD), U10.3 (VCC), U11.3 (VCC), U12.3 (VCC), U13.3 (VCC), VR1.1 (CCW)
/ACT_ENA: R24.2, U7.26 (PB0)
/ACT_ENB: R23.2, U7.27 (PB1)
/ACT_IN1: R22.2, U7.33 (PB12)
/ACT_IN2: R21.2, U7.34 (PB13)
/ACT_IN3: R20.2, U7.35 (PB14)
/ACT_IN4: R19.2, U7.36 (PB15)
/ADC_ACCEL: ACCEL1.2, C30.1, R29.2, U7.10 (PC2)
/ADC_BRAKE: ADC_BRAKE1.2, C28.1, R28.2, U7.9 (PC1)
/ADC_STEER: C31.1, U7.8 (PC0), VR1.2 (WIPER)
/BNO_INT: J7.1, U7.57 (PB5)
/BNO_RST: J6.4 (Pin_4_4), U7.56 (PB4)
/CANH_1: J5.1, R4.2, U12.7 (CANH), U13.7 (CANH)
/CANH_2: R5.1, R6.1, U10.7 (CANH), U11.7 (CANH)
/CANL_1: J5.2, R4.1, U12.6 (CANL), U13.6 (CANL)
/CANL_2: R5.2, R6.2, U10.6 (CANL), U11.6 (CANL)
/DHT11_DATA: DHT1.1, U7.39 (PC8)
/F446_CAN1_RX: U4.44 (PA11), U13.4 (R)
/F446_CAN1_TX: U4.45 (PA12), U13.1 (D)
/F446_CAN2_RX: U7.44 (PA11), U11.4 (R)
/F446_CAN2_TX: U7.45 (PA12), U11.1 (D)
/H723_FDCAN1_RX: J2.2, U12.4 (R)
/H723_FDCAN1_TX: J2.1, U12.1 (D)
/H723_FDCAN2_RX: J2.4, U10.4 (R)
/H723_FDCAN2_TX: J2.3, U10.1 (D)
/I2C1_SCL: J7.3, U7.61 (PB8)
/I2C1_SDA: J7.2, U7.62 (PB9)
/LED_BRAKE: R12.1, U7.20 (PA4)
/LED_LEFT: R10.1, U7.14 (PA0)
/LED_RIGHT: R11.1, U7.15 (PA1)
/LED_STATUS: R13.1, U7.21 (PA5)
/ND_BOOT0: R3.1, U7.60 (BOOT0)
/ND_NRST: C3.1, J4.5, U7.7 (NRST)
/ND_OSC_IN: C23.1, U7.5 (PH0), Y3.1 (IN/OUT)
/ND_OSC_OUT: C24.1, U7.6 (PH1), Y3.3 (OUT/IN)
/ND_SWCLK: J4.2, U7.49 (PA14)
/ND_SWDIO: J4.4, U7.46 (PA13)
/ND_SWO: J4.6, U7.55 (PB3)
/ND_VCAP1: C22.1, U7.30 (VCAP_1)
/PB2_1: R7.1, U4.28 (PB2)
/PB2_2: R8.1, U7.28 (PB2)
/RB_BOOT0: R2.1, U4.60 (BOOT0)
/RB_NRST: C2.1, J3.5, U4.7 (NRST)
/RB_OSC_IN: C26.1, U4.5 (PH0), Y4.1 (IN/OUT)
/RB_OSC_OUT: C27.1, U4.6 (PH1), Y4.3 (OUT/IN)
/RB_SWCLK: J3.2, U4.49 (PA14)
/RB_SWDIO: J3.4, U4.46 (PA13)
/RB_SWO: J3.6, U4.55 (PB3)
/RB_VCAP1: C9.1, U4.30 (VCAP_1)
/SERVO_PWM: J10.3, U4.22 (PA6)
/TOGGLE_SW: C25.1, R9.2, SW1.1, U7.11 (PC3)
/UART_RX_1: J8.2, U4.17 (PA3)
/UART_RX_2: J9.2, U7.17 (PA3)
/UART_TX_1: J8.1, U4.16 (PA2)
/UART_TX_2: J9.1, U7.16 (PA2)
/US_ECHO: R1.2, R15.1, U7.58 (PB6)
/US_TRIG: J11.2, U7.29 (PB10)
GND: C1.2, C2.2, C3.2, C4.2, C5.2, C6.2, C7.2, C8.2, C9.2, C10.2, C11.2, C12.2, C13.2, C14.2, C15.2, C16.2, C17.2, C18.2, C19.2, C20.2, C21.2, C22.2, C23.2, C24.2, C25.2, C26.2, C27.2, C28.2, C29.2, C30.2, C31.2, C32.2, D1.1 (K), D2.1 (K), D3.1 (K), D4.1 (K), D5.1 (K), DHT1.3, J1.2, J2.5, J2.6, J3.3, J4.3, J5.3, J7.4, J8.3, J9.3, J10.2, J11.4, R2.2, R3.2, R7.2, R8.2, R15.2, R28.1, R29.1, SW1.2, U1.1 (GND), U4.12 (VSSA), U4.18 (VSS), U4.31 (VSS), U4.47 (VSS), U4.63 (VSS), U7.12 (VSSA), U7.18 (VSS), U7.31 (VSS), U7.47 (VSS), U7.63 (VSS), U10.2 (GND), U10.8 (RS), U11.2 (GND), U11.8 (RS), U12.2 (GND), U12.8 (RS), U13.2 (GND), U13.8 (RS), VR1.3 (CW), Y3.2 (GND), Y3.4 (GND__1), Y4.2 (GND)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
unnamed: D1.2 (A), R14.2
unnamed: D2.2 (A), R10.2
unnamed: D3.2 (A), R11.2
unnamed: D4.2 (A), R12.2
unnamed: D5.2 (A), R13.2
unnamed: J11.3, R1.1
unnamed: R24.1, front2.1
unnamed: R23.1, front2.2
unnamed: R22.1, front2.3
unnamed: R21.1, front2.4
unnamed: R20.1, front2.5
unnamed: R19.1, front2.6
VCC: C1.1, J1.1, J10.1, J11.1, U1.3 (VI)

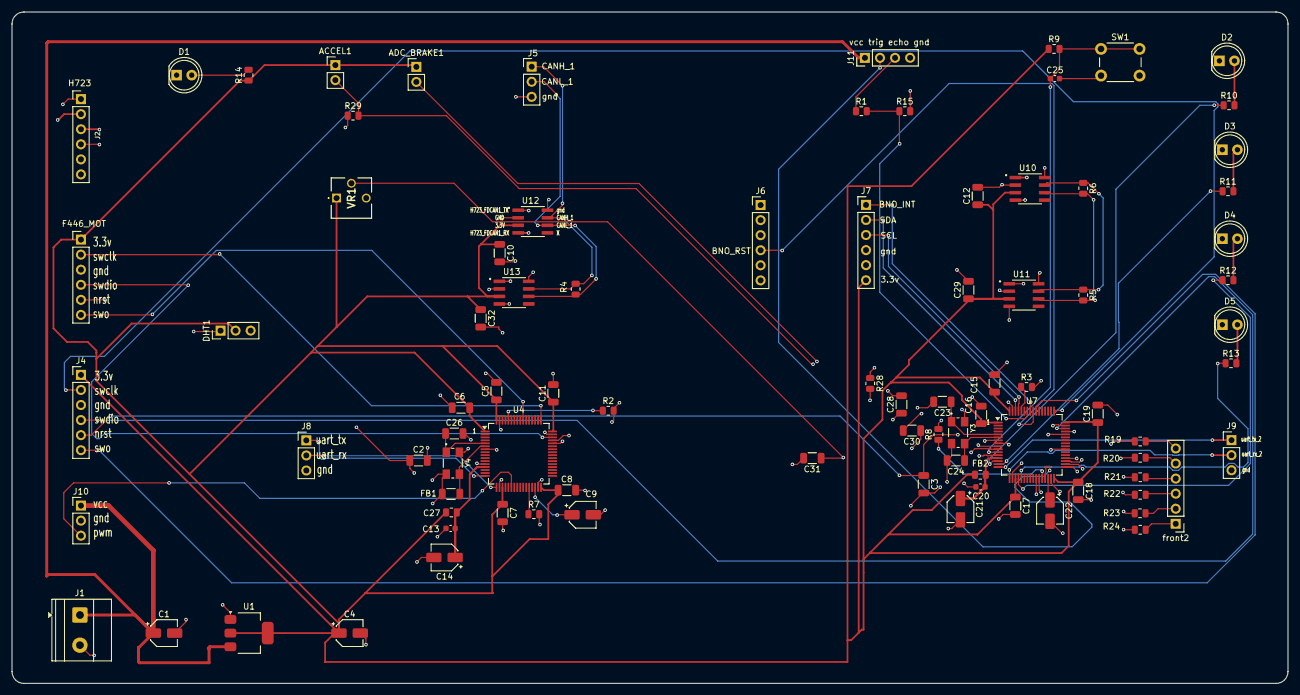
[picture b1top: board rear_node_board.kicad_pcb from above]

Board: 4 copper layers, 215.1 x 113.2 mm, 88 parts (0 on the bottom side), 73 nets.
